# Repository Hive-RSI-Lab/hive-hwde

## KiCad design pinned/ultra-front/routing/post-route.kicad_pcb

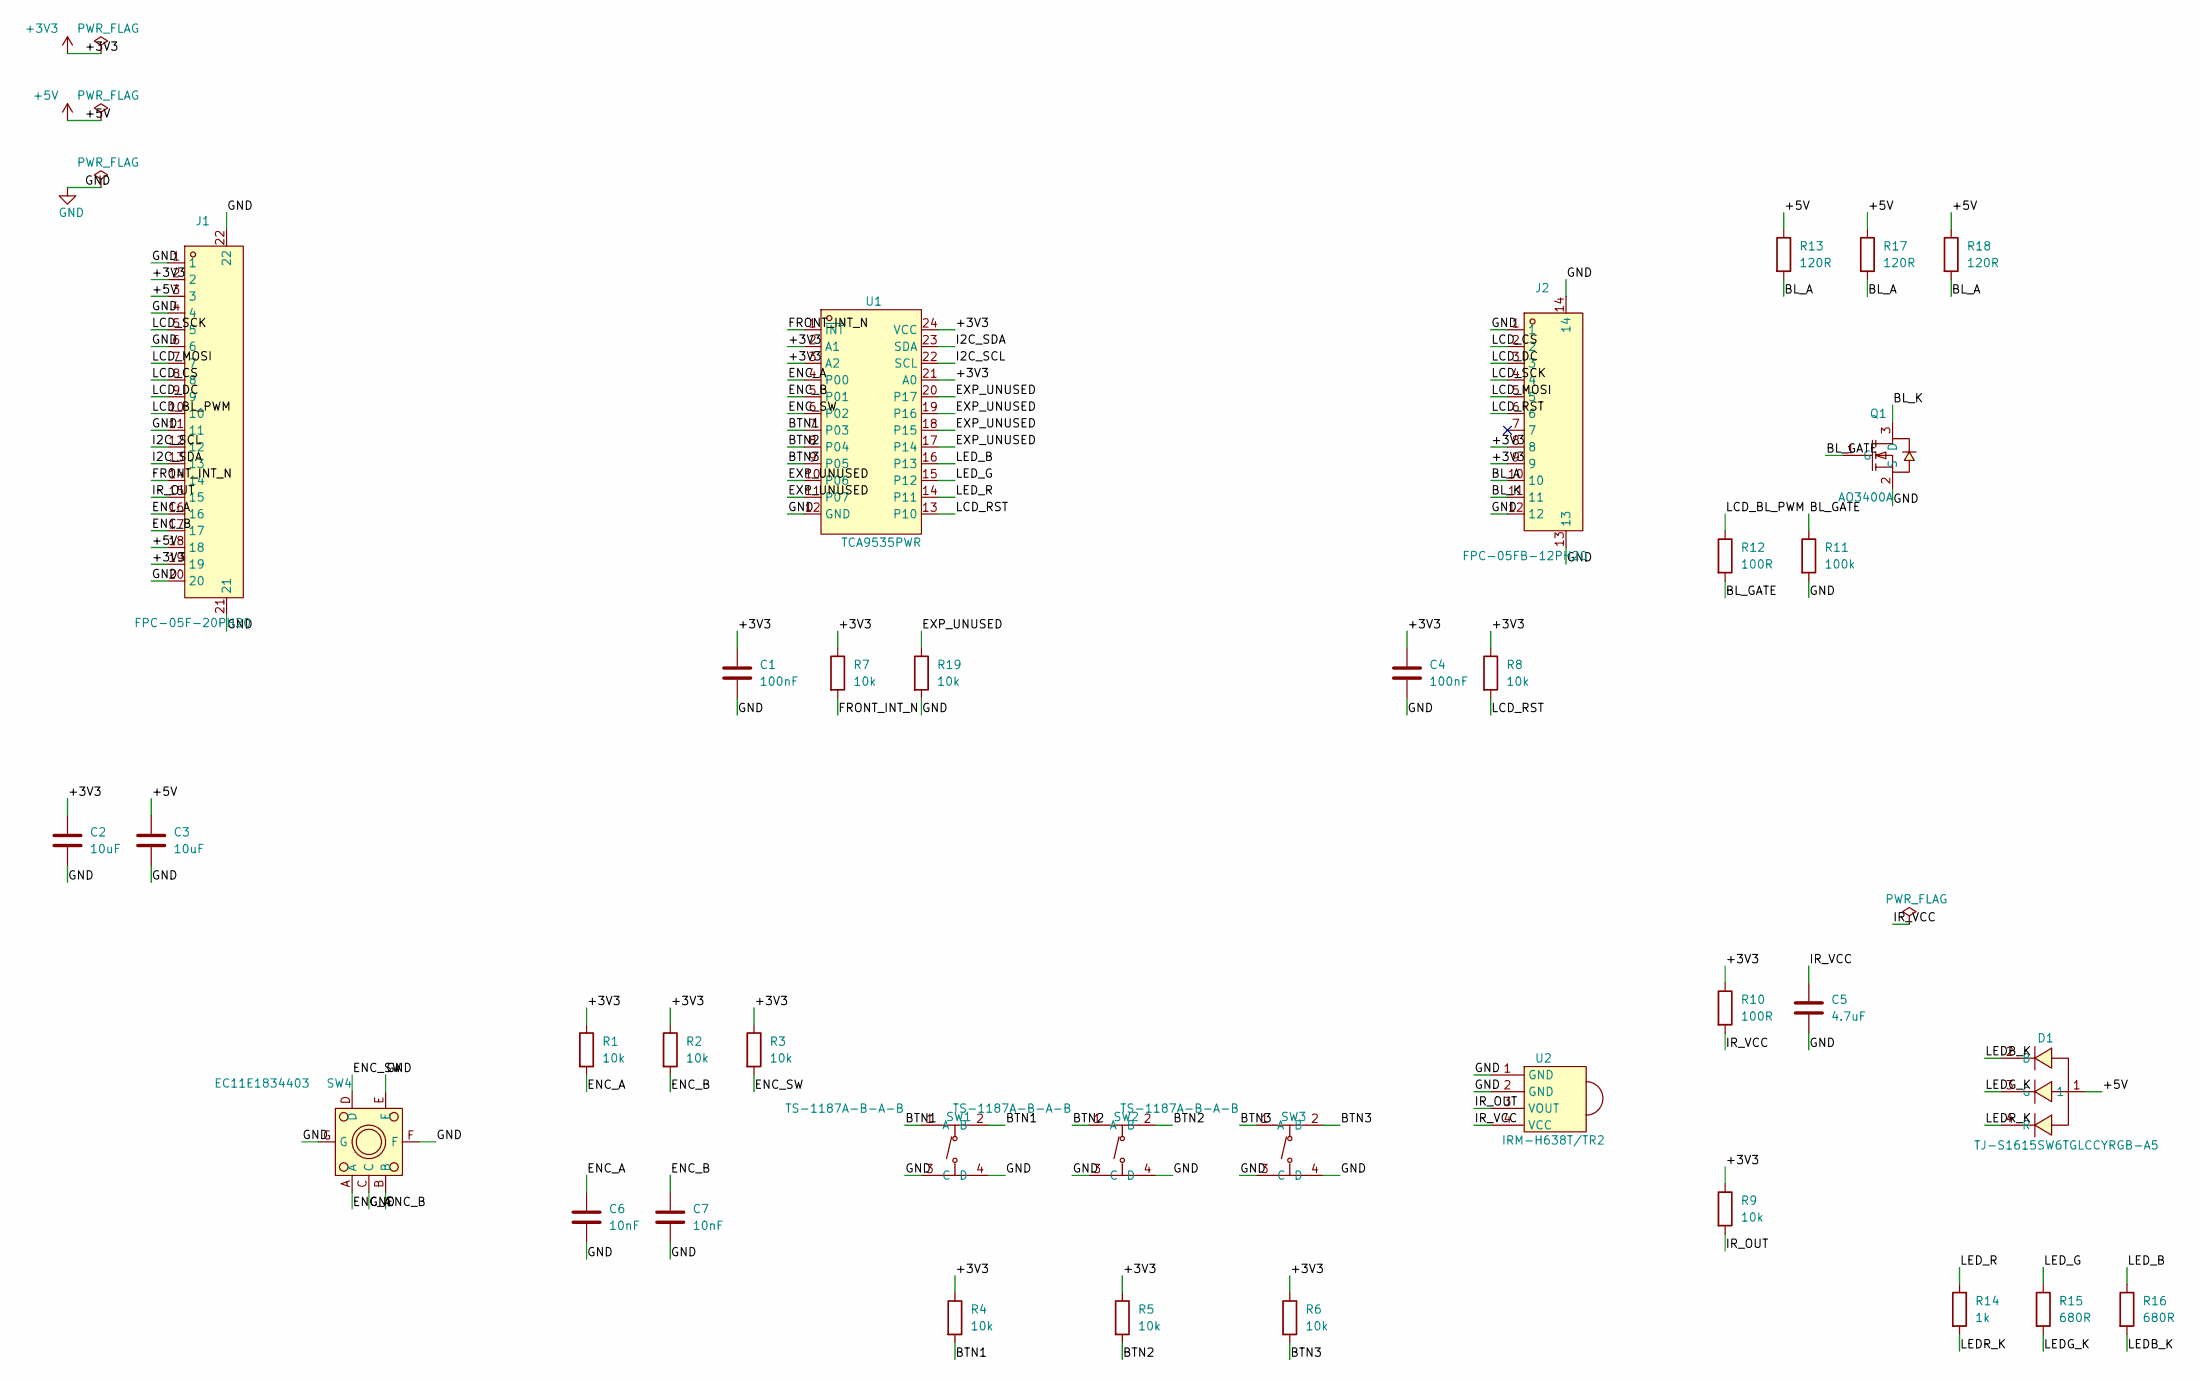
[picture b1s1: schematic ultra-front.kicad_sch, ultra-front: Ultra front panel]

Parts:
C1, C4: 100nF; C0603
C2, C3: 10uF; C0805
C5: 4.7uF; C0603
C6, C7: 10nF; C0603
D1: TJ-S1615SW6TGLCCYRGB-A5; LED-SMD_4P-L1.6-W1.5-TR
J1: FPC-05F-20PH20; FPC-SMD_20P-P0.50_XUNPU_FPC-05F-20PH20
J2: FPC-05FB-12PH20; FPC-SMD_12P-P0.50_XUNPU_FPC-05FB-12PH20
Q1: AO3400A; SOT-23-3_L2.9-W1.3-P1.90-LS2.4-BR
R1, R2, R3, R4, R5, R6, R7, R8, R9, R19: 10k; R0603
R10, R12: 100R; R0603
R11: 100k; R0603
R13, R17, R18: 120R; R0603
R14: 1k; R0603
R15, R16: 680R; R0603
SW1, SW2, SW3: TS-1187A-B-A-B; SW-SMD_4P-L5.1-W5.1-P3.70-LS6.5-TL_H1.5
SW4: EC11E1834403; SW-TH_EC11E1820402
U1: TCA9535PWR; TSSOP-24_L7.8-W4.4-P0.65-LS6.4-BL
U2: IRM-H638T/TR2; SENSOR-SMD_IRM-H638T-TR2-TL

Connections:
+3V3: C1.1, C2.1, C4.1, J1.2, J1.19, J2.8, J2.9, R1.1, R2.1, R3.1, R4.1, R5.1, R6.1, R7.1, R8.1, R9.1, R10.1, U1.2 (A1), U1.3 (A2), U1.21 (A0), U1.24 (VCC)
+5V: C3.1, D1.1, J1.3, J1.18, R13.1, R17.1, R18.1
/BL_A: J2.10, R13.2, R17.2, R18.2
/BL_GATE: Q1.1 (G), R11.1, R12.2
/BL_K: J2.11, Q1.3 (D)
/BTN1: R4.2, SW1.1 (A), SW1.2 (B), U1.7 (P03)
/BTN2: R5.2, SW2.1 (A), SW2.2 (B), U1.8 (P04)
/BTN3: R6.2, SW3.1 (A), SW3.2 (B), U1.9 (P05)
/ENC_A: C6.1, J1.16, R1.2, SW4.A, U1.4 (P00)
/ENC_B: C7.1, J1.17, R2.2, SW4.B, U1.5 (P01)
/ENC_SW: R3.2, SW4.D, U1.6 (P02)
/EXP_UNUSED: R19.1, U1.10 (P06), U1.11 (P07), U1.17 (P14), U1.18 (P15), U1.19 (P16), U1.20 (P17)
/FRONT_INT_N: J1.14, R7.2, U1.1 (~INT)
/I2C_SCL: J1.12, U1.22 (SCL)
/I2C_SDA: J1.13, U1.23 (SDA)
/IR_OUT: J1.15, R9.2, U2.3 (VOUT)
/IR_VCC: C5.1, R10.2, U2.4 (VCC)
/LCD_BL_PWM: J1.10, R12.1
/LCD_CS: J1.8, J2.2
/LCD_DC: J1.9, J2.3
/LCD_MOSI: J1.7, J2.5
/LCD_RST: J2.6, R8.2, U1.13 (P10)
/LCD_SCK: J1.5, J2.4
/LEDB_K: D1.2 (B), R16.2
/LEDG_K: D1.3 (G), R15.2
/LEDR_K: D1.4 (R), R14.2
/LED_B: R16.1, U1.16 (P13)
/LED_G: R15.1, U1.15 (P12)
/LED_R: R14.1, U1.14 (P11)
GND: C1.2, C2.2, C3.2, C4.2, C5.2, C6.2, C7.2, J1.1, J1.4, J1.6, J1.11, J1.20, J1.21, J1.22, J2.1, J2.12, J2.13, J2.14, Q1.2 (S), R11.2, R19.2, SW1.3 (C), SW1.4 (D), SW2.3 (C), SW2.4 (D), SW3.3 (C), SW3.4 (D), SW4.C, SW4.E, SW4.F, SW4.G, U1.12 (GND), U2.1 (GND), U2.2 (GND); also elsewhere on the board

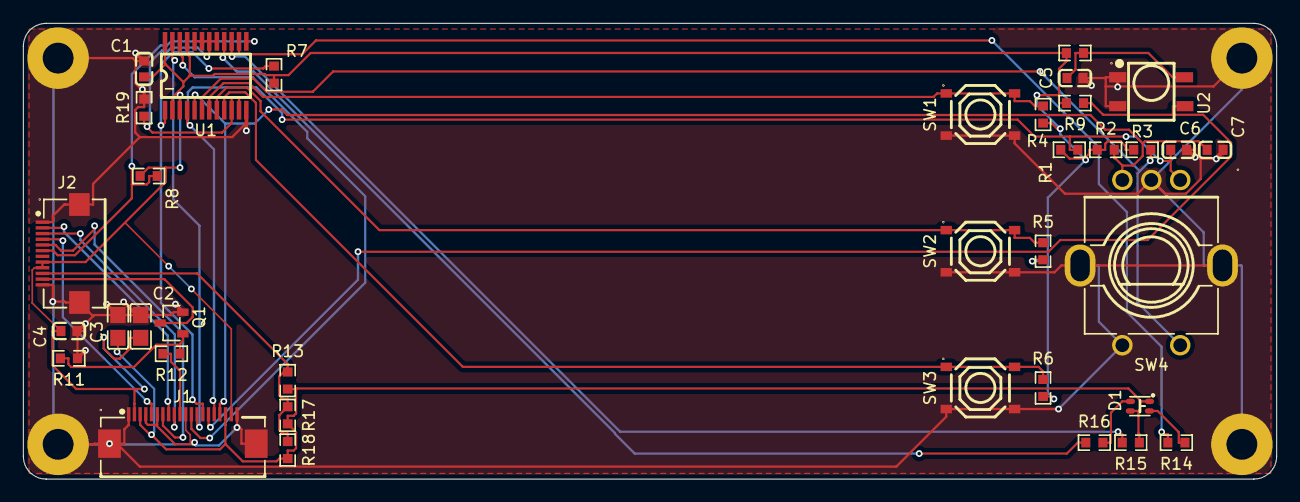
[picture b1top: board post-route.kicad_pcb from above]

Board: 2 copper layers, 110.0 x 40.0 mm, 40 parts (0 on the bottom side), 30 nets.

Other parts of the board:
H1, H2, H3, H4: MountingHole_2.7mm_M2.5_Pad

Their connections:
GND: H1.1, H2.1, H3.1, H4.1; also elsewhere on the board

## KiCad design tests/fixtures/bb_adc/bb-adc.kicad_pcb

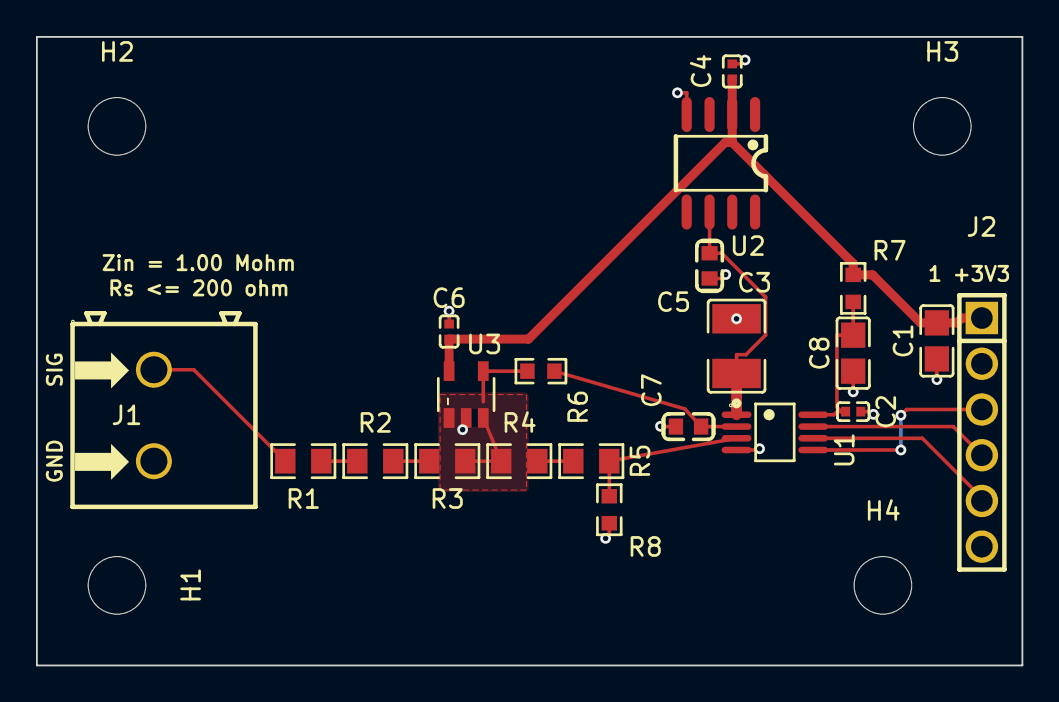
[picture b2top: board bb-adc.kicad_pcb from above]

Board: 2 copper layers, 54.8 x 34.9 mm, 25 parts (0 on the bottom side), 15 nets.

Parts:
C1, C8: 10uF 25V X5R; C0805
C2, C4, C6: 100nF 16V X7R; C0402
C3: 47uF 16V X7R; C1210
C5: 2.2uF 10V X7R; C0603
C7: 1nF 50V C0G/NP0; C0603
H1, H2, H3, H4: M3_3.2mm; MountingHole_3.2mm_M3
J1: WJ500V-5.08-2P; CONN-TH_2P-P5.00_WJ500V-5.08-2P
J2: 1x6P 2.54mm male header; HDR-TH_6P-P2.54-V-M-1
R1, R2, R3, R4, R5: 200K 0.02% 10ppm/C; R0805
R6: 49.9 ohm 1%; R0603
R7: 10 ohm 1%; R0603
R8: 0 ohm 1%; R0603
U1: ADS8326IB; VSSOP-8_L3.0-W3.0-P0.65-LS5.0-BL
U2: ADR4520B; SOIC-8_L5.0-W4.0-P1.27-LS6.0-BL
U3: OPA320; SOT-23-5_L3.0-W1.7-P0.95-LS2.8-BR

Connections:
+3V3: C1.1, C4.1, C6.1, J2.1, R7.1, U2.2, U3.5
/AGND_SENSE: R5.2, R8.1, U1.3
/AIN_ADC: C7.1, R6.2, U1.2
/AIN_BUF: R6.1, U3.1, U3.4
/AIN_DIV: R3.2, R4.1, U3.3
/AIN_RAW: J1.1, R1.1
/ATT_A: R1.2, R2.1
/ATT_B: R2.2, R3.1
/ATT_C: R4.2, R5.1
/CS: J2.3, U1.5
/DOUT: J2.5, U1.6
/SCLK: J2.4, U1.7
GND: C1.2, C2.2, C3.2, C4.2, C5.2, C6.2, C7.2, C8.2, J1.2, J2.2, J2.6, R8.2, U1.4, U2.4, U3.2
VDD_ADC: C2.1, C8.1, R7.2, U1.8
VREF: C3.1, C5.1, U1.1, U2.6
